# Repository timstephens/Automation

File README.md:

# Automation
Home automation and monitoring based on MQTT and ESP8266. There are a series of nodes, which can function as a producer or consumer of messages (or both). Right now, there are three types of node:

* Temperature sensor nodes, which have a small temperature sensor and broadcast the reading every few seconds (a PCB exists for these).
* Switcher nodes, which contain a relay to switch stuff on and off (a PCB exists for low-voltage switching)
* Message board nodes, which contain an LED matrix display so that output can be communicated to the real world.

These nodes each connect to an MQTT broker, which could be something like Mosquitto running on a Raspberry Pi. There's then some glue logic that needs to exist (e.g. NodeRed) that allows the whole system to respond to changes on the inputs. Some work is requred to get all this working, and this is left as an exercise for the student.

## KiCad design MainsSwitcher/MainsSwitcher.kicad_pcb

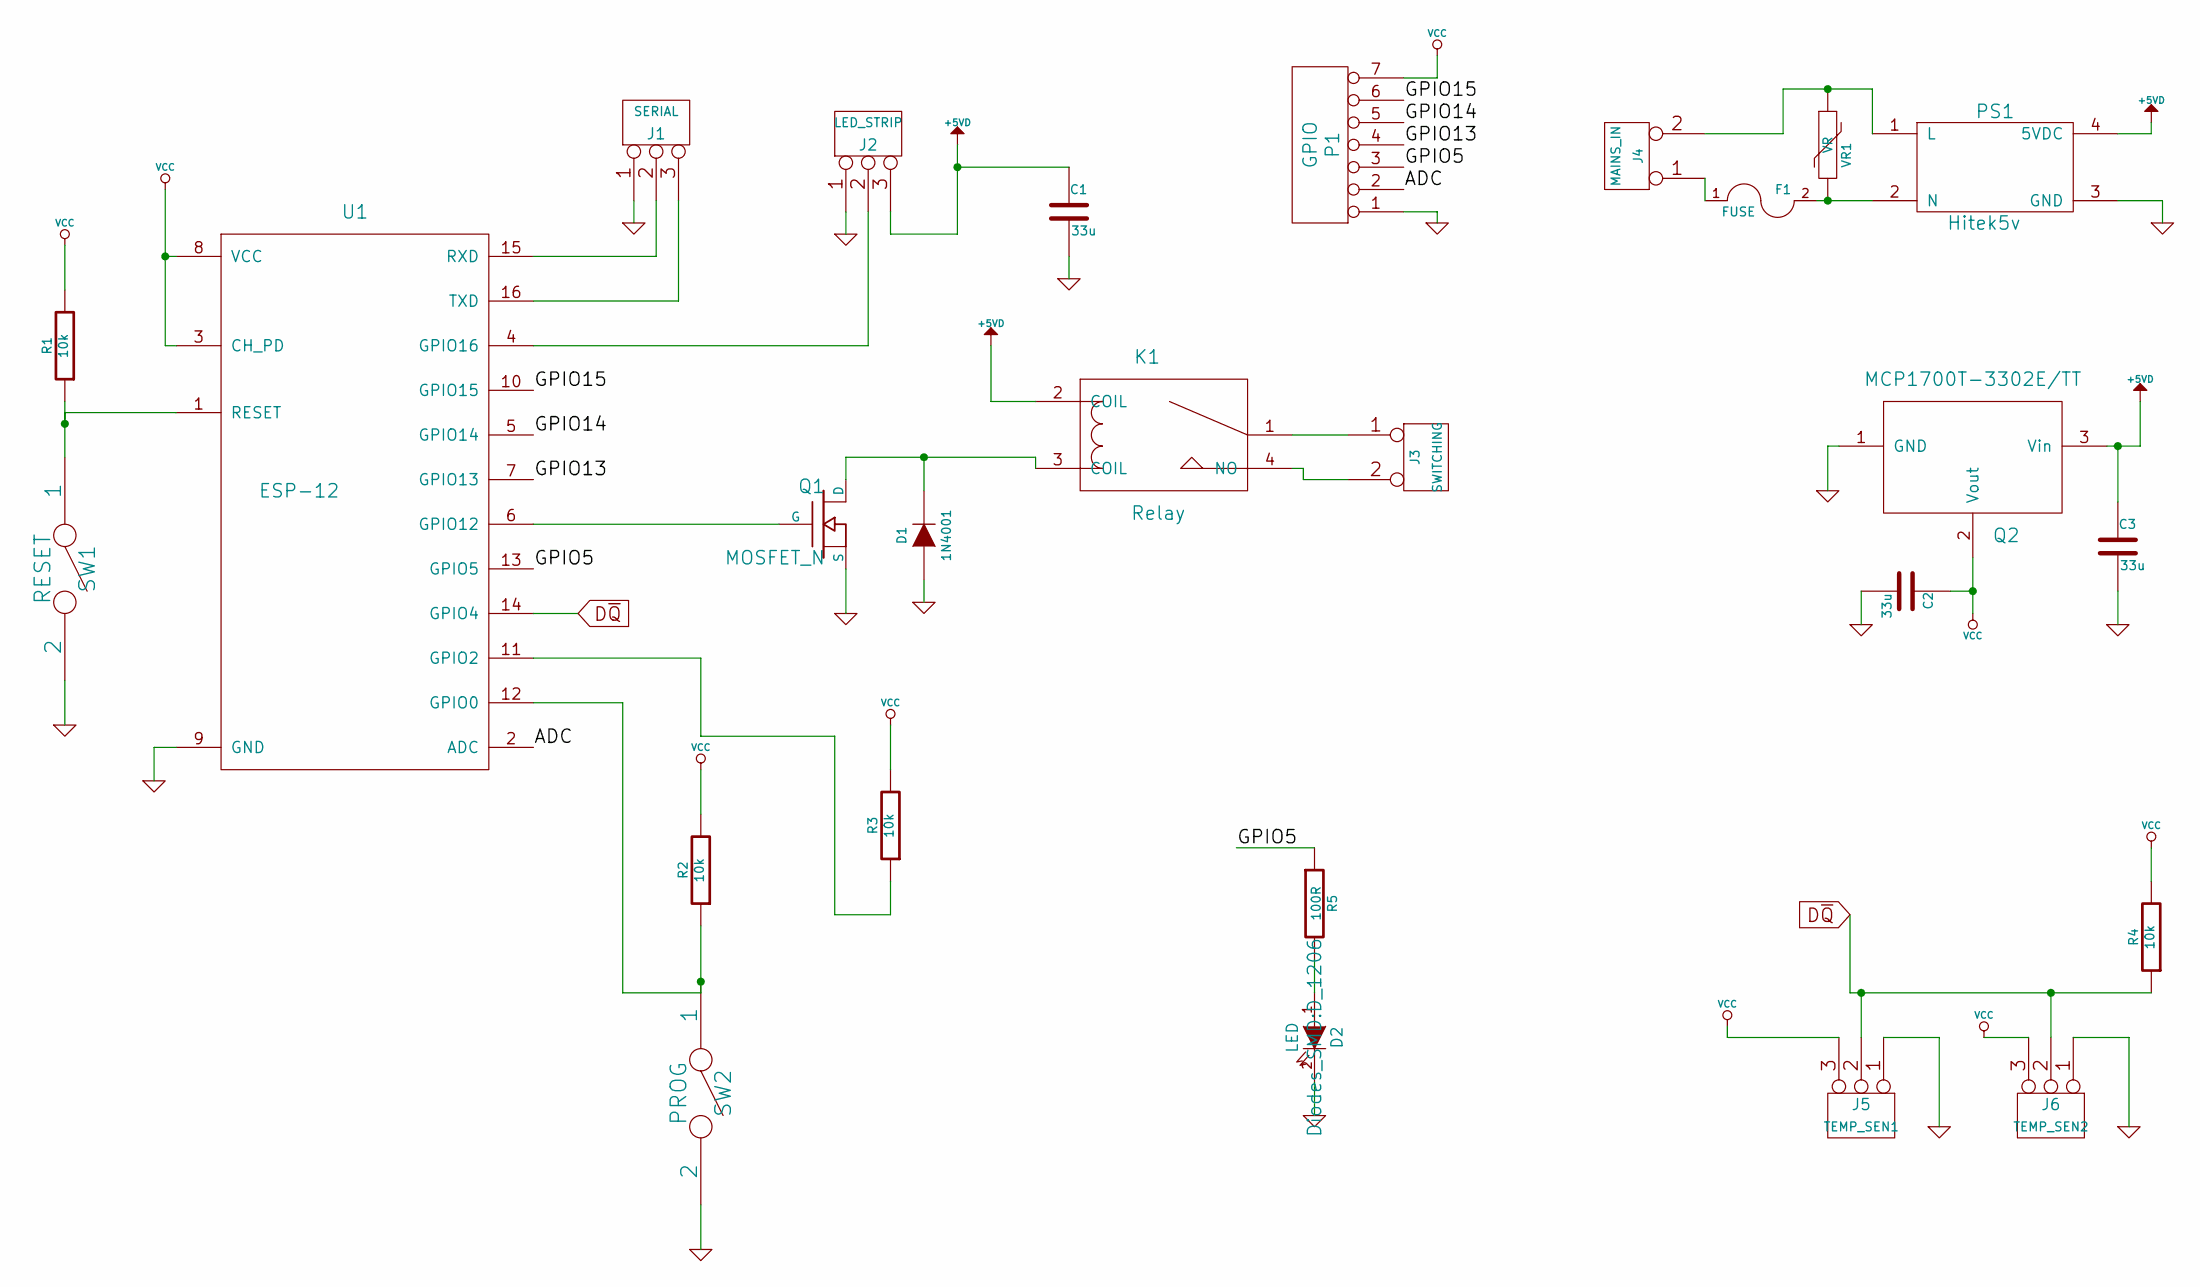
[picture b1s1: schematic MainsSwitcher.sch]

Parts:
C1, C2, C3: 33u; C_1206_HandSoldering
D1: 1N4001; D_SMA-SMB_Universal_Handsoldering
D2: LED; D_1206
F1: FUSE; Schurter_Fuseholder(20x5mm)0031.8211
J1: SERIAL; Molex_KK-6410-03_03x2.54mm_Straight
J2: LED_STRIP; Molex_KK-6410-03_03x2.54mm_Straight
J3: SWITCHING; PhoenixContact_PT1,5-2-5.0-V
J4: MAINS_IN; PhoenixContact_PT1,5-2-5.0-V
J5: TEMP_SEN1; Molex_KK-6410-03_03x2.54mm_Straight
J6: TEMP_SEN2; Molex_KK-6410-03_03x2.54mm_Straight
K1: Relay; COTO_SIP_ReedRelay-9007-05-00
P1: GPIO; Molex_KK-6410-07_07x2.54mm_Straight
PS1: Hitek5v; HLK-P0X
Q1: MOSFET_N; SOT-23_Handsoldering
Q2: MCP1700T-3302E/TT; SOT-23
R1, R2, R3, R4: 10k; R_1206_HandSoldering
R5: 100R; R_1206_HandSoldering
SW1: RESET; SW_PUSH_6mm
SW2: PROG; SW_PUSH_6mm
U1: ESP-12
VR1: VR; MOV-EPCOS-B72214S0421K101

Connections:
+5VD: C1.1, C3.1, J2.3, K1.2 (COIL), PS1.4 (5VDC), Q2.3 (Vin)
/ADC: P1.2, U1.2 (ADC)
/GPIO5: P1.3, R5.1, U1.13 (GPIO5)
/GPIO13: P1.4, U1.7 (GPIO13)
/GPIO14: P1.5, U1.5 (GPIO14)
/GPIO15: P1.6, U1.10 (GPIO15)
D~Q: J5.2 (PM), J6.2 (PM), R4.1, U1.14 (GPIO4)
GND: C1.2, C2.2, C3.2, D1.1 (A), D2.2 (K), J1.1, J2.1, J5.1, J6.1, P1.1, PS1.3 (GND), Q1.S, Q2.1 (GND), SW1.2, SW2.2, U1.9 (GND)
unnamed: D1.2 (K), K1.3 (COIL), Q1.D
unnamed: D2.1 (A), R5.2
unnamed: F1.1, J4.1
unnamed: F1.2, PS1.2 (N), VR1.2
unnamed: J1.2 (PM), U1.15 (RXD)
unnamed: J1.3, U1.16 (TXD)
unnamed: J2.2 (PM), U1.4 (GPIO16)
unnamed: J3.1, K1.1
unnamed: J3.2 (PM), K1.4 (NO)
unnamed: J4.2 (PM), PS1.1 (L), VR1.1
unnamed: Q1.G, U1.6 (GPIO12)
unnamed: R1.1, SW1.1, U1.1 (RESET)
unnamed: R2.1, SW2.1, U1.12 (GPIO0)
unnamed: R3.1, U1.11 (GPIO2)
VCC: C2.1, J5.3, J6.3, P1.7, Q2.2 (Vout), R1.2, R2.2, R3.2, R4.2, U1.3 (CH_PD), U1.8 (VCC)

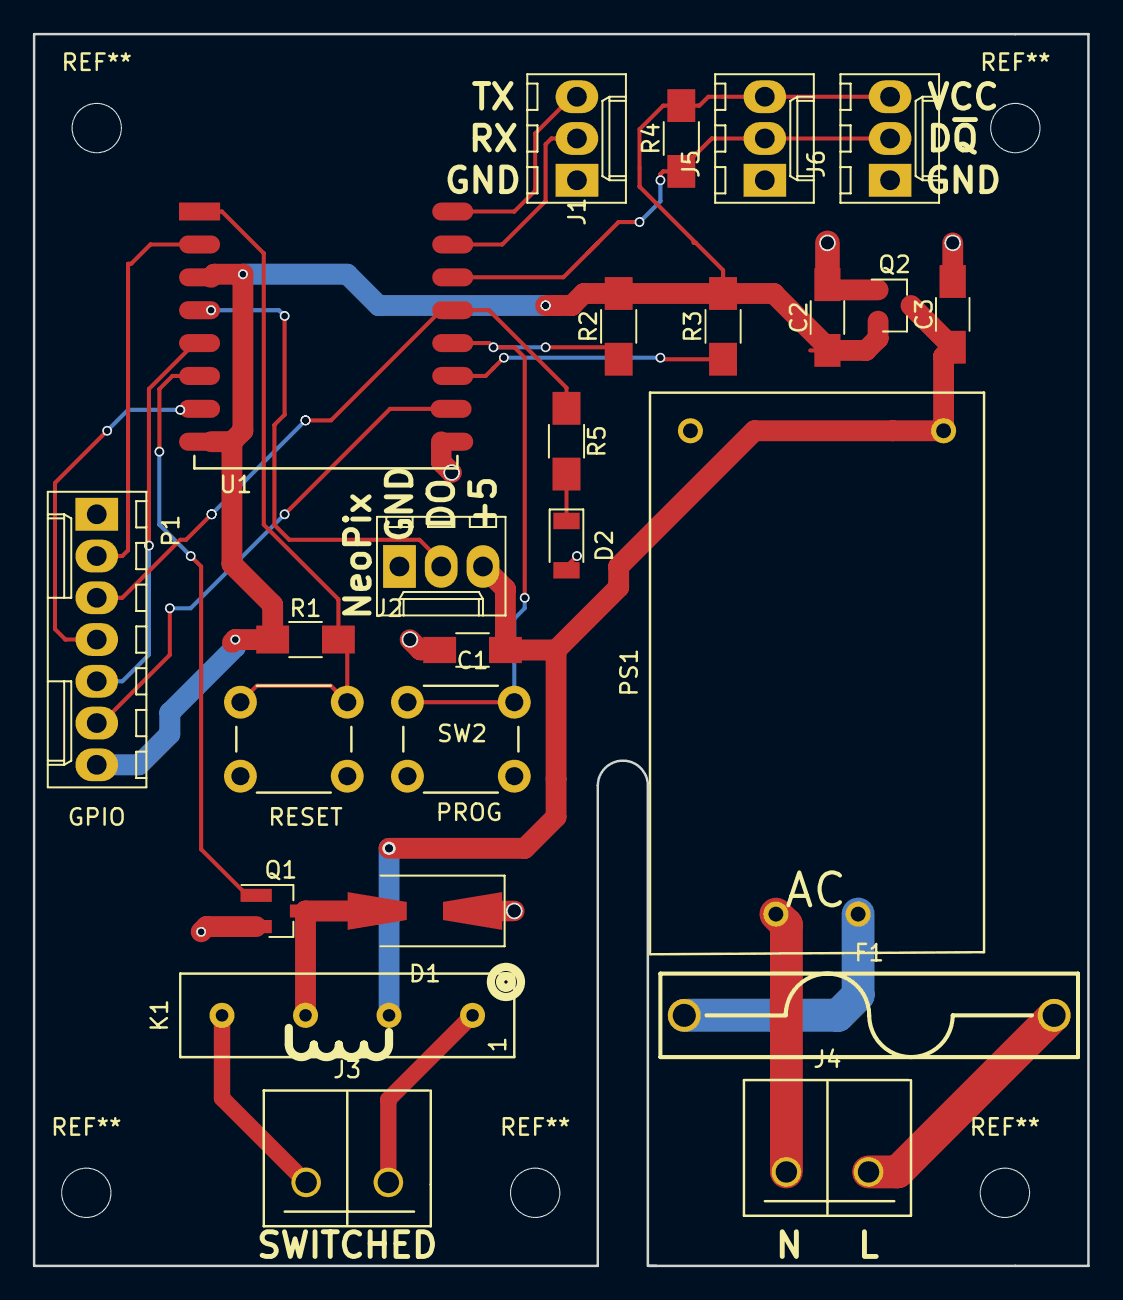
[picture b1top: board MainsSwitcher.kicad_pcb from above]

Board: 2 copper layers, 64.1 x 74.9 mm, 25 parts (0 on the bottom side), 23 nets.

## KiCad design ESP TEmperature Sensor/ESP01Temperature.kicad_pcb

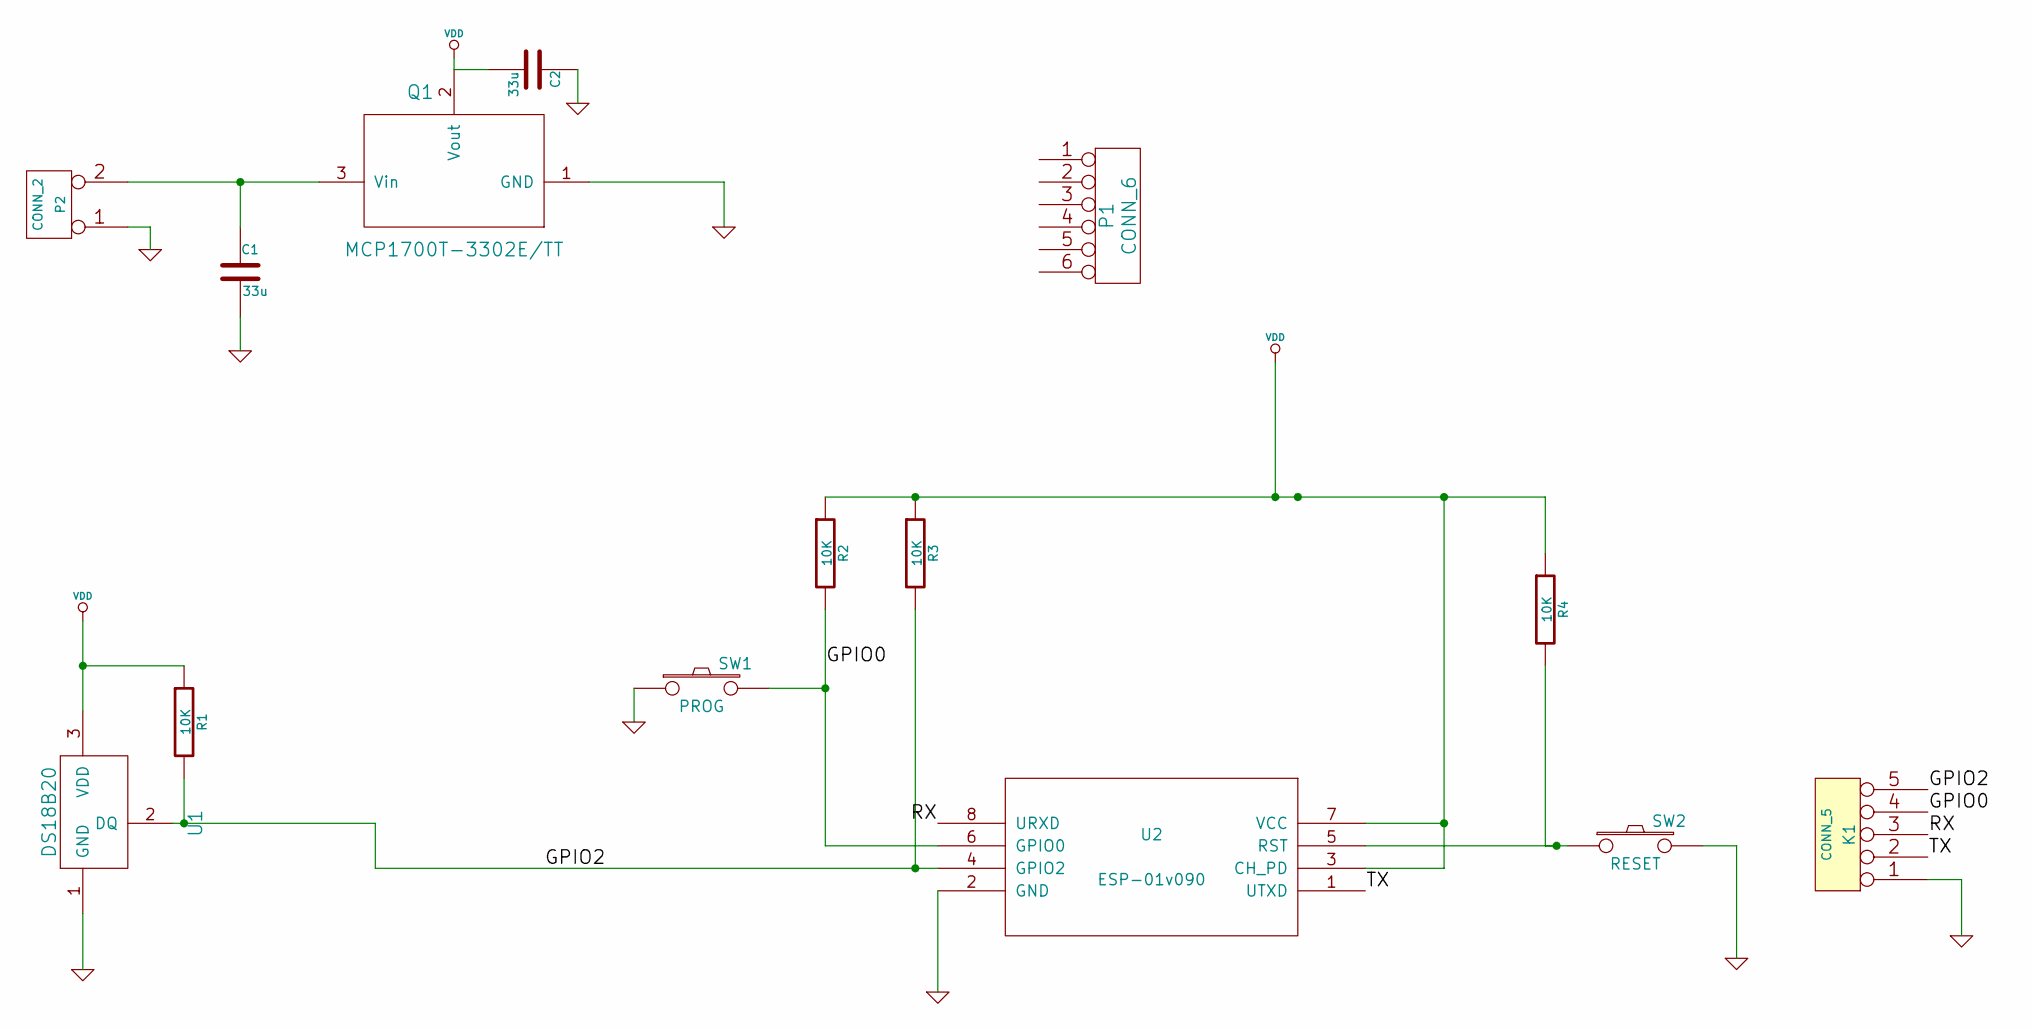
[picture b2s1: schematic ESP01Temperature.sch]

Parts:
C1, C2: 33u; C_1206_HandSoldering
K1: CONN_5; Molex_KK-6410-05_05x2.54mm_Straight
P1: CONN_6; Molex_KK-6410-06_06x2.54mm_Straight
P2: CONN_2; Pin_Header_Angled_1x02
Q1: MCP1700T-3302E/TT; SOT-23
R1, R2, R3, R4: 10K; R_1206_HandSoldering
SW1: PROG; SW_PUSH_6mm
SW2: RESET; SW_PUSH_6mm
U1: DS18B20; TO-92_Molded_Narrow
U2: ESP-01v090; ESP-01

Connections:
/GPIO0: K1.4, R2.2, SW1.2, U2.6 (GPIO0)
/GPIO2: K1.5, R1.2, R3.2, U1.2 (DQ), U2.4 (GPIO2)
/RX: K1.3, U2.8 (URXD)
/TX: K1.2, U2.1 (UTXD)
GND: C1.2, C2.1, K1.1, P2.1, Q1.1 (GND), SW1.1, SW2.2, U1.1 (GND), U2.2 (GND)
unnamed: C1.1, P2.2 (PM), Q1.3 (Vin)
unnamed: R4.2, SW2.1, U2.5 (RST)
VDD: C2.2, Q1.2 (Vout), R1.1, R2.1, R3.1, R4.1, U1.3 (VDD), U2.3 (CH_PD), U2.7 (VCC)

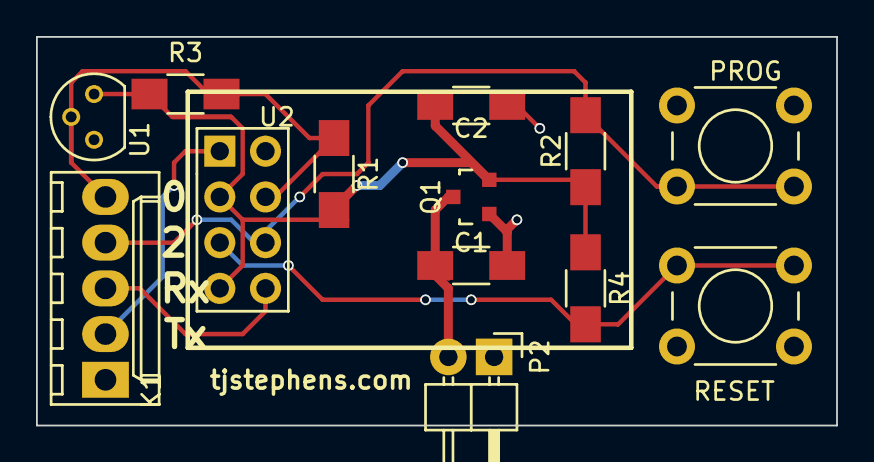
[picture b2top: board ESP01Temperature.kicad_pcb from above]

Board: 2 copper layers, 44.4 x 21.6 mm, 13 parts (0 on the bottom side), 8 nets.

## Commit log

2015-04-27 Initial Commit
    MQTT_Publish contains some code that connects to a mosquitto server and
    publishes the temperature measured on a DS18B20. The code then holds a
    delay and pushes an update every 10s. The whole thing may or may not
    work depending on whether the connection remains open or not. A version
    very similar to this (but without the ESP.deepsleep() on line 96 worked
    for 10hours without failure in the initial test.
2015-05-25 Trying to get subscribes to work
2015-06-29 Add SensorTelemetry
    which is supposed to be able to get the temperature from a DHT22 T/H
    sensor and send it over RF24 link.
2015-07-08 Add new receiver code
    Not yet functional —receiver does not appear togged anything from
    radio.available on the pong side of the system.
    Radio on ping side claims about 50% success rate. Something is fibbing
    to me…
2015-07-18 LED Matrix as first step towards MQTT display
    LED Matrix allows writing of arbitrary characters to a set of LED
    matrix displays controlled by MAX7219 chips. The particular orientation
    of the displays may differ (they’re from eBay).
    Added font.h, which is cribbed from
    http://www.hwsw.no/snippets/5x7_LCD_font.php
    NB: To run this on an ESP8266, you need to make a change like this to
2015-07-19 Working display of millis() on ESP8266
2015-07-19 Working with debug info to Serial
2015-07-19 Working with wifi connection to network
    IP Address gathered.
2015-07-19 Wifi connection works, broker connection fails
    WiFi network connection starts up with the system, and remains up (ping
    proves this).
    Added MQTT stuff, but there’s nothing working here. Issue seems to be
    that it doesn’t connect to the broker (or fails). Nothing shows on
    mosquito_sub on the broker end either, so it’s a double-ended fail.
    Counter increments (slowly) since there’s a delay incurred with
2015-07-20 rename client to prevent naming clash
    created function to clear displays
    More debugging
2015-08-24 Trying to get the wifi and broker to connect
2015-08-24 Revert 3d2e02d..628b364
    This rolls back to commit 3d2e02dde2a0b45e62e666465407c8845c5f7a7e.
2016-03-28 trying to debug
2016-03-28 Working to display millis(), and connects to wifi
2016-03-28 Getting there
    LED Matrix displays millis()
    Connects to WiFi and MQTT broker, publishes and receives messages with
    confirmation through Serial connection
2016-03-28 Working MQTT publishing to LED Matrix display
2016-03-28 Working with full LED matrix
    Includes a validation element to catch the case when the buffer
    overflows.
2016-04-06 Added a temperature sensor node
    UNTESTED. Not yet uploaded to an ESP to confirm that it’s behaving…
2016-04-09 Add message scrolling to the display
    This will now scroll the message if it’s longer than the number of
    characters available on the display. Once through the whole message,
    then displays the first N characters on the display until the next
    message arrives.
2016-04-16 Working for DHT11, apart from the DHT11 part
    There’s something screwy with the DHT11 that I have, or my wiring for
    it, or the power supply to it. For this reason, it’s not returning
    sensible data. The data that it does return is faithfully published on
    MQTT though…
2016-04-16 Working to publish temperatures
    This works in isolation, but with a second ESP acting as the LED
    Matrix, the two seem to be competing for something, so they spend all
    their time reconnecting. Not clear whether this is something in the
    server that’s kicking each one off when the other tries to connect, or
    whether it’s a network thing…
2016-05-05 Rename to make things work
2016-08-20 Adding code to handle button
    Hardware works with the modifications required for this code.
2016-10-03 Working to publish MQTT
    This needs GPIO0 and GPIO2 on an ESP01 to be pulled high to get it to
    boot and run. If either is pulled low, the ESP01 will drop into the
    boot loader, and never run the code.
2016-10-10 Working temperature broadcast
    Using DS18b20 sensor, this is actually working again!
2016-10-16 Sleeping enabled
    5 minute sleep after successfully posting a temperature report
2016-10-17 PCB for temperature sensor
2016-11-04 PCB Design
    Kicad design files for build PCB
2016-11-06 SSID/Password config by web page
    Added code to use ESP8266Websserver to offer a page to allow a client
    to connect to configure the wifi settings.
    This code still assumes that the MQTT server will exist at a fixed IP
    (needs a DNS resolver adding to fix this), and perhaps a method to
    configure the hostname and store it to EEPROM.
    TODO
2016-11-12 Config server, and sleep
    Configuration web server that opens a soft access point, and offers a
    webpage that allows configuration of the SSID, password for the main
    wifi network, and IP address of the MQTT broker.
    Needs some tidying up of the page, and proper handler that returns some
    sort of configuration confirmation, etc.
    Once correctly connected, sends the temperature reading from the
2016-11-13 Updated config form, removed sleep
    The code isn’t waking from deepsleep. It seems like there’s a bug in
    the code somewhere, so I don’t know if this is solvable.
2016-11-13 Revert "Config server, and sleep"
    This reverts commit aa25cd490c7b3ed2b0cc843134b077d644cdfd3d.
    # Conflicts:
    # temperatureSensor/temperatureSensor.ino
2016-11-13 Revert "Revert "Config server, and sleep""
    This reverts commit 66553d52c90a2edec54f977f60f120cf252b75a4.
2016-11-13 Functional
2017-02-15 First stab at switch responder
    Modified the code so that the device should respond to calls on the
    /control topic and switch the state of an IO pin.
2017-02-16 Delete a couple of unused items
    Files that were only there for debugging - removed them.
2017-02-26 Circuitboard for Mains Switcher
    PCB for the Multi-switcher design. Can accept volt free switching via
    relay, WS8212, some free GPIO.
    Powered from HLK-P01 5v psu connected to the mains on board.
2017-02-27 Added fuseholder
    Fuseholder added to the mains inlet. As ordered.
2017-03-04 Compiles, doesn't run
    Gives a fatal exception on the Serial output once it’s finished
    uploading.
2017-03-04 Does work
    It was the programmer that was misbehaving, not the code.
2017-03-04 Moved around the TempSensor node for more reliability too
    Matches what is in the GP Switcher node.
2017-03-04 Forgot to add the reliability code
    Added reliability code to the loop() of TemperatureSensor.
2017-03-05 Refactor
    Moved a bunch of the wifi setup stuff into a separate .h file
2017-03-05 Updated the TempSensor
    code now refactored to be a bit neater…
2017-03-13 multiple sensors on TempSensor
    Added the ability for the TempSensor to address multiple DS18b20s.
    It’ll report the value of each in a different sub-topic.
    These ought to be deterministic, so should always have the same
    relationship...
2017-03-22 Working and installed
    Couple of changes to accommodate a layout error on the PCB (GPIOs are
    incorrectly identified on library part)
    Made the code that sets the relay more generic (uses constants rather
    than pin numbers at point of use).
2019-02-21 Changes to who knows what.
    Uncommitted changes to stuff. Tidying up…
